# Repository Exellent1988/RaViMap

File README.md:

# RasViMap:
##INSTALL NOTES
	INSTALL OLA
	INSTALL node.js
	INSTALL python2.7
	PI-Monitor

##TODOS

##mainly:

- [ ] PI-WISE:
	- [ ] installscript
	- [ ] WLAN-Script
	- [ ] Autostart-scripts
	- [ ] Chromium/(better alternative) +kioskmode +presentationmode
	- [ ] STATUS-outputs (own site/ pimonitor plugin?)

- [ ] FUNCTIONS:
	- [ ] DMX-read:
		- [ ] DMX(max 10 channels):
		- [ ] videoauswahl
		- [ ] dimmer
		- [ ] rgb /farbkorrektur
		- [ ] shutter
		- [ ] gobos/masken/rahmen/effekte
		- [ ] speed/splay/stop
		- [ ] scale
		- [ ] x / y Transform (presets für Position?)

- [ ] WEBSERVER:
	- [ ] Admin-Backend
	- [ ] Templates
	- [ ] autoconverter
	- [ ] auto source-list creator

##secondly:

-	[ ] 2x16 DISPLAY Integration
- [ ] ArtNet-Integration

##THE IDEA
###FUNCTIONS:
*	trasformation
*	warper
*	playlist
*	softedge
*	layer
*	2zeilen display (status)
*	Defaults /Templates;

Betriebsmodi;
- Single(DMX)
- Pro(ArtNet)
- Multi(ArtNet)

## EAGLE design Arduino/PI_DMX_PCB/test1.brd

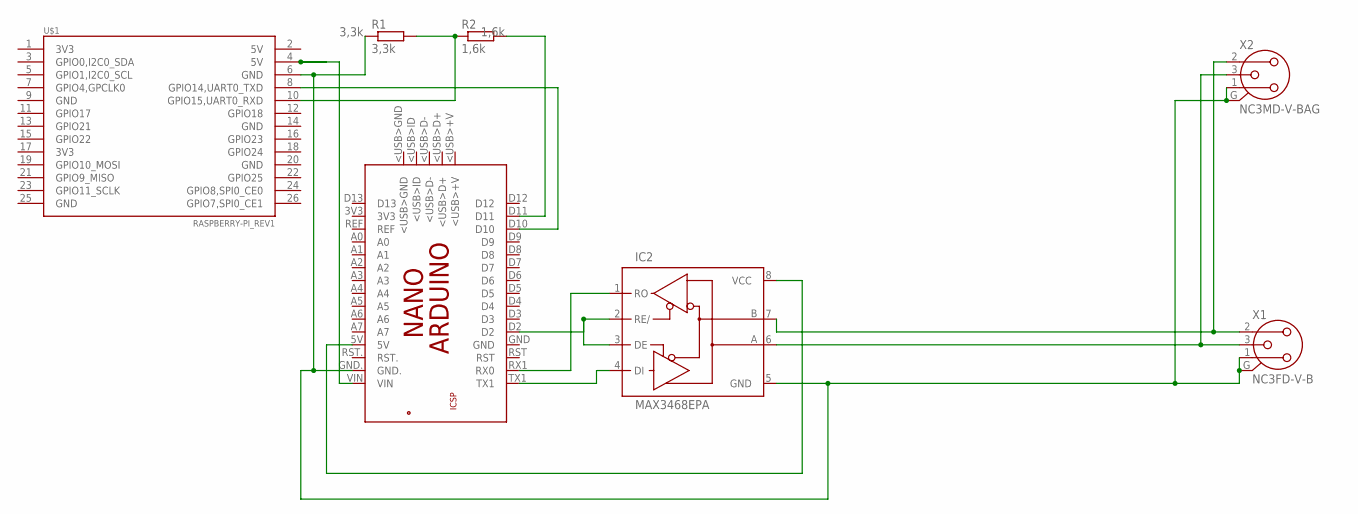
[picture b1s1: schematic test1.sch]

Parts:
IC2: MAX3468EPA; DIL08
PCB1: ARDUINO_NANO
R1: 3,3k; 0204/7
R2: 1,6k; 0204/7
U$1: RASPBERRY-PI_REV1
X1: NC3FD-V-B
X2: NC3MD-V-BAG

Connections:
unnamed: IC2.4 (DI), PCB1.TX1
unnamed: IC2.2 (RE/), IC2.3 (DE), PCB1.D2
unnamed: PCB1.VIN, U$1.4 (5V)
unnamed: IC2.1 (RO), PCB1.RX1 (RX0)
unnamed: IC2.7 (B), X1.2 (1), X2.2 (1)
unnamed: IC2.6 (A), X1.3, X2.3
unnamed: PCB1.D11, R2.2
unnamed: IC2.8 (VCC), PCB1.5V
unnamed: R1.2, R2.1, U$1.10 (GPIO15,UART0_RXD)
unnamed: IC2.5 (GND), PCB1.GND., R1.1, U$1.6 (GND), X1.1 (2), X1.G, X2.1 (2), X2.G
unnamed: PCB1.D10, U$1.8 (GPIO14,UART0_TXD)

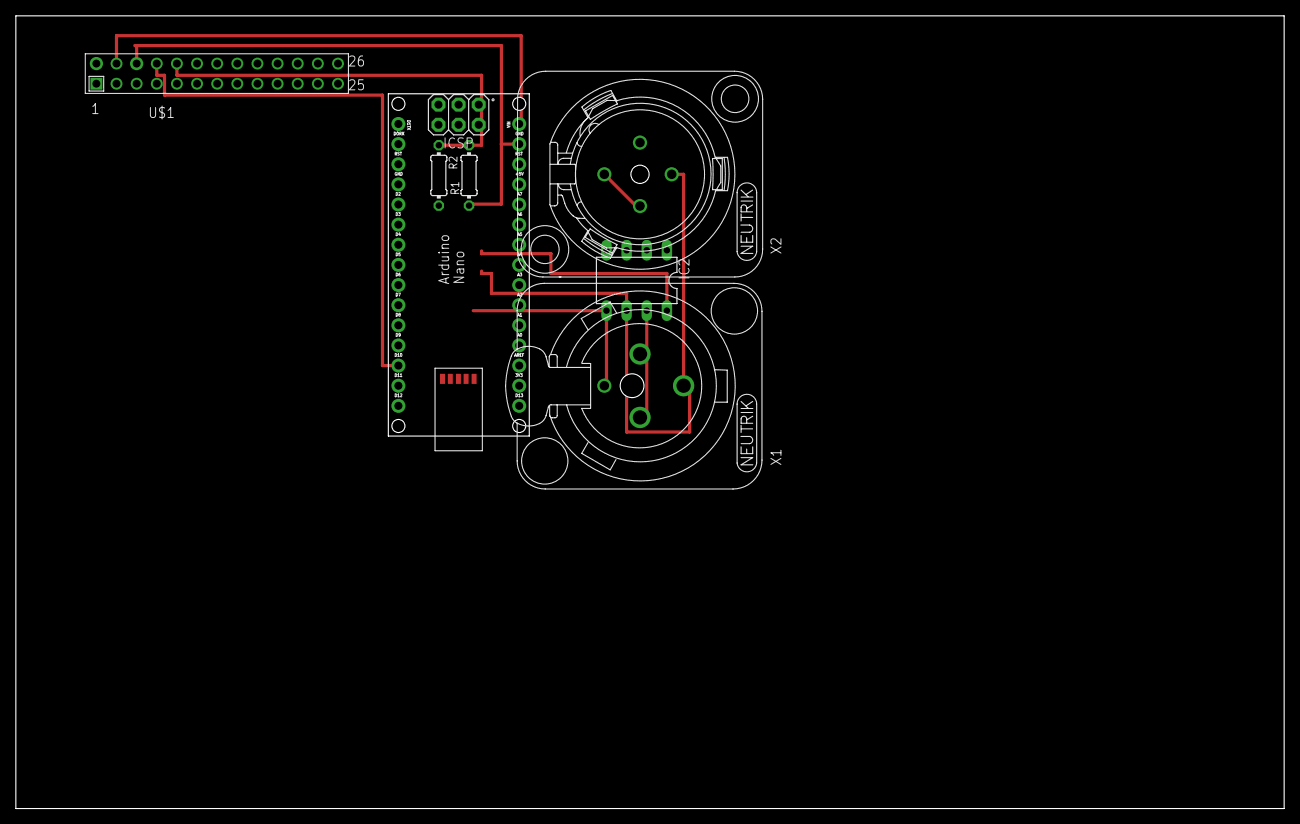
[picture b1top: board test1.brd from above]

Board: 2 copper layers, 160.0 x 100.0 mm, 7 parts (0 on the bottom side), 11 nets.

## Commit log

2016-04-26 new Readme
2016-05-12 New Readme, scripts which lyed around
2016-05-12 new layout
2016-05-12 new layout readme
2016-05-12 add gitignore
2016-06-09 new scripts
2016-06-09 test app
2016-06-09 Working receive part!!
2016-06-09 new 10 channel test
2016-06-09 tzpo
2016-06-09 channel typo
2016-06-09 something strange
2016-06-15 some new stuff
2016-06-15 image correction
2016-06-15 sone slight changes
2016-06-15 typo
2016-06-15 wrong id
2016-06-15 wrong stuff
2016-06-15 console log
2016-06-15 + vergessen
2016-06-15 substract image size
2016-06-15 width /2
2016-06-15 body overflow hidden
2016-06-15 rotation
2016-06-15 error in rotation
2016-06-15 scale
2016-06-15 misslining
2016-06-15 klammer
2016-06-15 new crop factor
2016-06-15 new crop
